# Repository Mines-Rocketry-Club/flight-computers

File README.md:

# Mines Rocket Club Flight Computer Development
## Scope
The series of flight computers produced as part of this project are inteneded to be useable for any low or high power rocketry applications.
These will also span a large range of cost in order to provide flight computer capabilities for very high risk and experimental flights.
The lowest possible trim level is a CW RF emmiter intended for use with radio direction finding equipment.
The highest trim level will provide a platform for executing user space code asynchronously from the main event loop of the flight computer.
## Standards
- No features* will be lost when moving up in trim levels.
<br>
*The Screamer's CW Emmiter is lost as the other telemetry hardware on the board can be used to locate the device.

## Trim Levels
|Name         |Features                                                                         |Weight |Cost (2024) |
|-------------|---------------------------------------------------------------------------------|-------|------------|
|The Screamer | CW RF Emitter                                                                   | 5g    | 5$         |
|The Timer    | 3 Axis Accelerometer, Barometric Altimiter, CP1200 Transmitter, 4 Pyro Channels | 10g   | 20$        |
|The Guesser  | GPS, Onboard Data Logging, WIFI based configuration                             | 15g   | 40$        |
|The Knower   | User Code Execution, High Frequency Data Logging, 8 Pyro Channels               | 20g   | 60$        |

## System Architectures
### The Screamer
#### Usage
This board emits a constant signal at 146.660 MHz.
This signal can be recived by many common low-cost trancievers, such as the Baofeng UV-5RA, UV8W, and AR-5RM.
With a directional antenna any of these trancievers provides radio direction finding capabilities to the system.
#### Design
The sysem does not have a microcontroller or any other regualtion system.
It consistis of a power supply, based on the <PART NAME> and the transmitter, which is a MAX2606 IF Oscillator.
This component is not intended to be used to drive an antenna directly, however, the internal 50Ω matching and the -10dBm power output provide enough for this usage.
In order to capture the full -10dBm output, a loop antenna must be attached to ***BOTH*** of the provided antenna pads.
Bare copper wire or thin coat magnet wire is recommened for the antenna. a single loop in the wire should be adequate for most applicatons.

Due to the extremley low power consumption of the system, it can be powered parasitically off of any of the other computers in this series.
> Attachement points will be added in the next revisions of each of the boards
> - [ ] The Timer
> - [ ] The Guesser
> - [ ] The Knower

### The Timer
#### Usage
#### Design
### The Guesser
### The Knower
## License
All hardware contained within this repository is under the TAPR Open Hardware License (OHL), which can be found, in full, in `HW_LICENSE`.
All software contained within this repository is under the GPL, which can be found, in full, in `FW_LICENSE`.

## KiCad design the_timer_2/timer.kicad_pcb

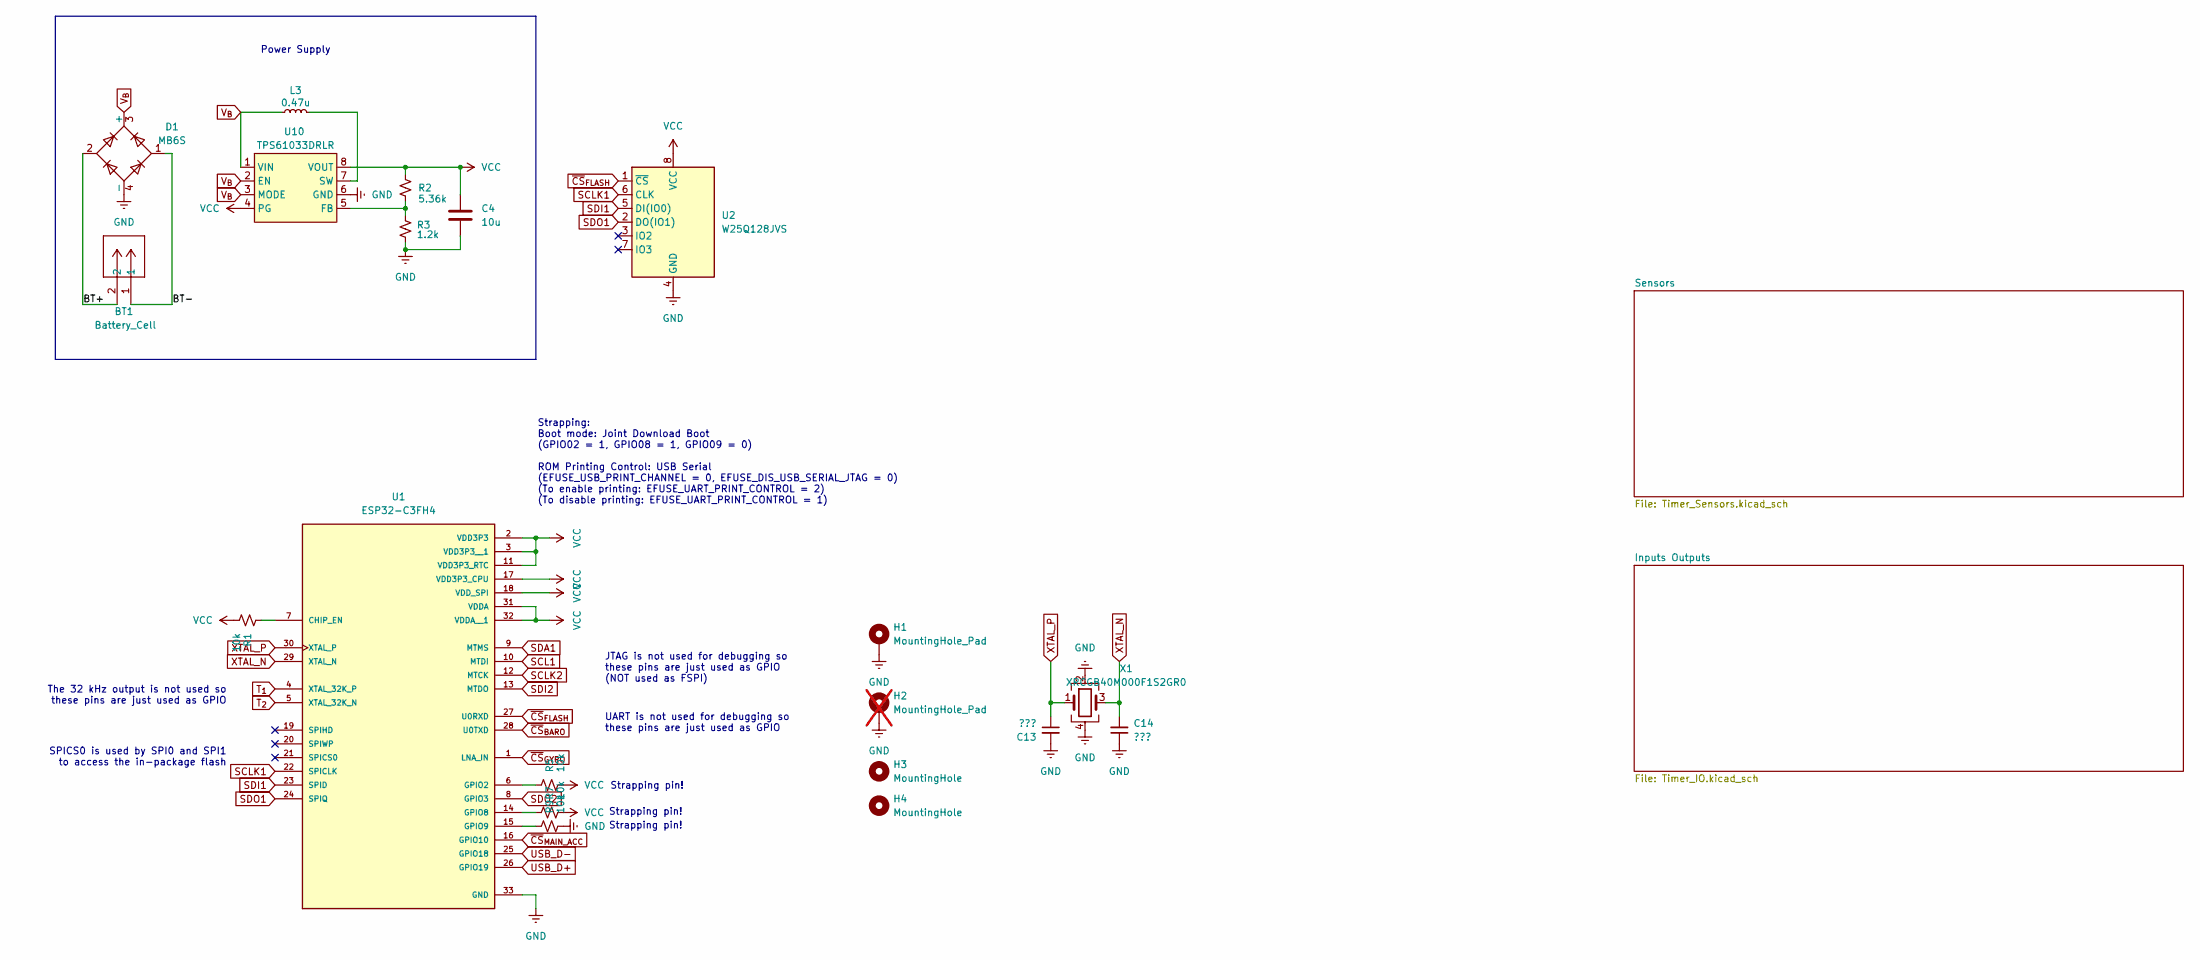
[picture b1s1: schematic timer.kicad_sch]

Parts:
BT1: Battery_Cell; CONN2_1775469-2_TEC
C4: 10u; C_0603_1608Metric
C13, C14: ???; C_0603_1608Metric
D1: MB6S; TO-269AA
H1: MountingHole_Pad; MountingHole_3.2mm_M3_Pad
H2: MountingHole_Pad; MountingHole_3.2mm_M3_Pad; not fitted
H3, H4: MountingHole; MountingHole_3.2mm_M3
L3: 0.47u; L_0603_1608Metric
R1, R5, R7, R9: 10k; R_0603_1608Metric
R2: 5.36k; R_0603_1608Metric
R3: 1.2k; R_0603_1608Metric
U1: ESP32-C3FH4; QFN-32-1EP_5x5mm_P0.5mm_EP3.7x3.7mm; PARTREV V1.0
U2: W25Q128JVS; SOIC-8_5.23x5.23mm_P1.27mm
U10: TPS61033DRLR; SOT-583-8
X1: XRCGB40M000F1S2GR0; Crystal_SMD_2016-4Pin_2.0x1.6mm

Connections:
/BT+: BT1.2, D1.2
/BT-: BT1.1, D1.1
GND: C4.2, C13.2, C14.1, D1.4 (-), H1.1, H2.1, R3.2, R9.2, U1.33 (GND), U2.4 (GND), U10.6 (GND), X1.2, X1.4; also elsewhere on the board
unnamed: R1.1, U1.7 (CHIP_EN)
unnamed: R5.1, U1.6 (GPIO2)
unnamed: R7.1, U1.14 (GPIO8)
unnamed: R9.1, U1.15 (GPIO9)
unnamed: R2.2, R3.1, U10.5 (FB)
unnamed: L3.1, U10.7 (SW)
SCL1: U1.10 (MTDI)
SCLK1: U1.22 (SPICLK), U2.6 (CLK)
SCLK2: U1.12 (MTCK); also elsewhere on the board
SDA1: U1.9 (MTMS)
SDI1: U1.23 (SPID), U2.5 (DI(IO0))
SDI2: U1.13 (MTDO); also elsewhere on the board
SDO1: U1.24 (SPIQ), U2.2 (DO(IO1))
SDO2: U1.8 (GPIO3); also elsewhere on the board
T_{1}: U1.4 (XTAL_32K_P); also elsewhere on the board
T_{2}: U1.5 (XTAL_32K_N); also elsewhere on the board
USB_D+: U1.26 (GPIO19); also elsewhere on the board
USB_D-: U1.25 (GPIO18); also elsewhere on the board
VCC: C4.1, R1.2, R2.1, R5.2, R7.2, U1.2 (VDD3P3), U1.3 (VDD3P3__1), U1.11 (VDD3P3_RTC), U1.17 (VDD3P3_CPU), U1.18 (VDD_SPI), U1.31 (VDDA), U1.32 (VDDA__1), U2.8 (VCC), U10.4 (PG), U10.8 (VOUT); also elsewhere on the board
V_{B}: D1.3 (+), L3.2, U10.1 (VIN), U10.2 (EN), U10.3 (MODE); also elsewhere on the board
XTAL_N: C14.2, U1.29 (XTAL_N), X1.3
XTAL_P: C13.1, U1.30 (XTAL_P), X1.1
~CS_{BARO}: U1.28 (U0TXD); also elsewhere on the board
~CS_{FLASH}: U1.27 (U0RXD), U2.1 (~CS)
~CS_{GYRO}: U1.1 (LNA_IN); also elsewhere on the board
~CS_{MAIN_ACC}: U1.16 (GPIO10); also elsewhere on the board

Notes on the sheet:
Strapping: Boot mode: Joint Download Boot (GPIO02 = 1, GPIO08 = 1, GPIO09 = 0) ROM Printing Control: USB Serial (EFUSE_USB_PRINT_CHANNEL = 0, EFUSE_DIS_USB_SERIAL_JTAG = 0) (To enable printing: EFUSE_UART_PRINT_CONTROL = 2) (To disable printing: EFUSE_UART_PRINT_CONTROL = 1)
UART is not used for debugging so these pins are just used as GPIO
SPICS0 is used by SPI0 and SPI1 to access the in-package flash
Strapping pin!
JTAG is not used for debugging so these pins are just used as GPIO (NOT used as FSPI)
Power Supply
The 32 kHz output is not used so these pins are just used as GPIO

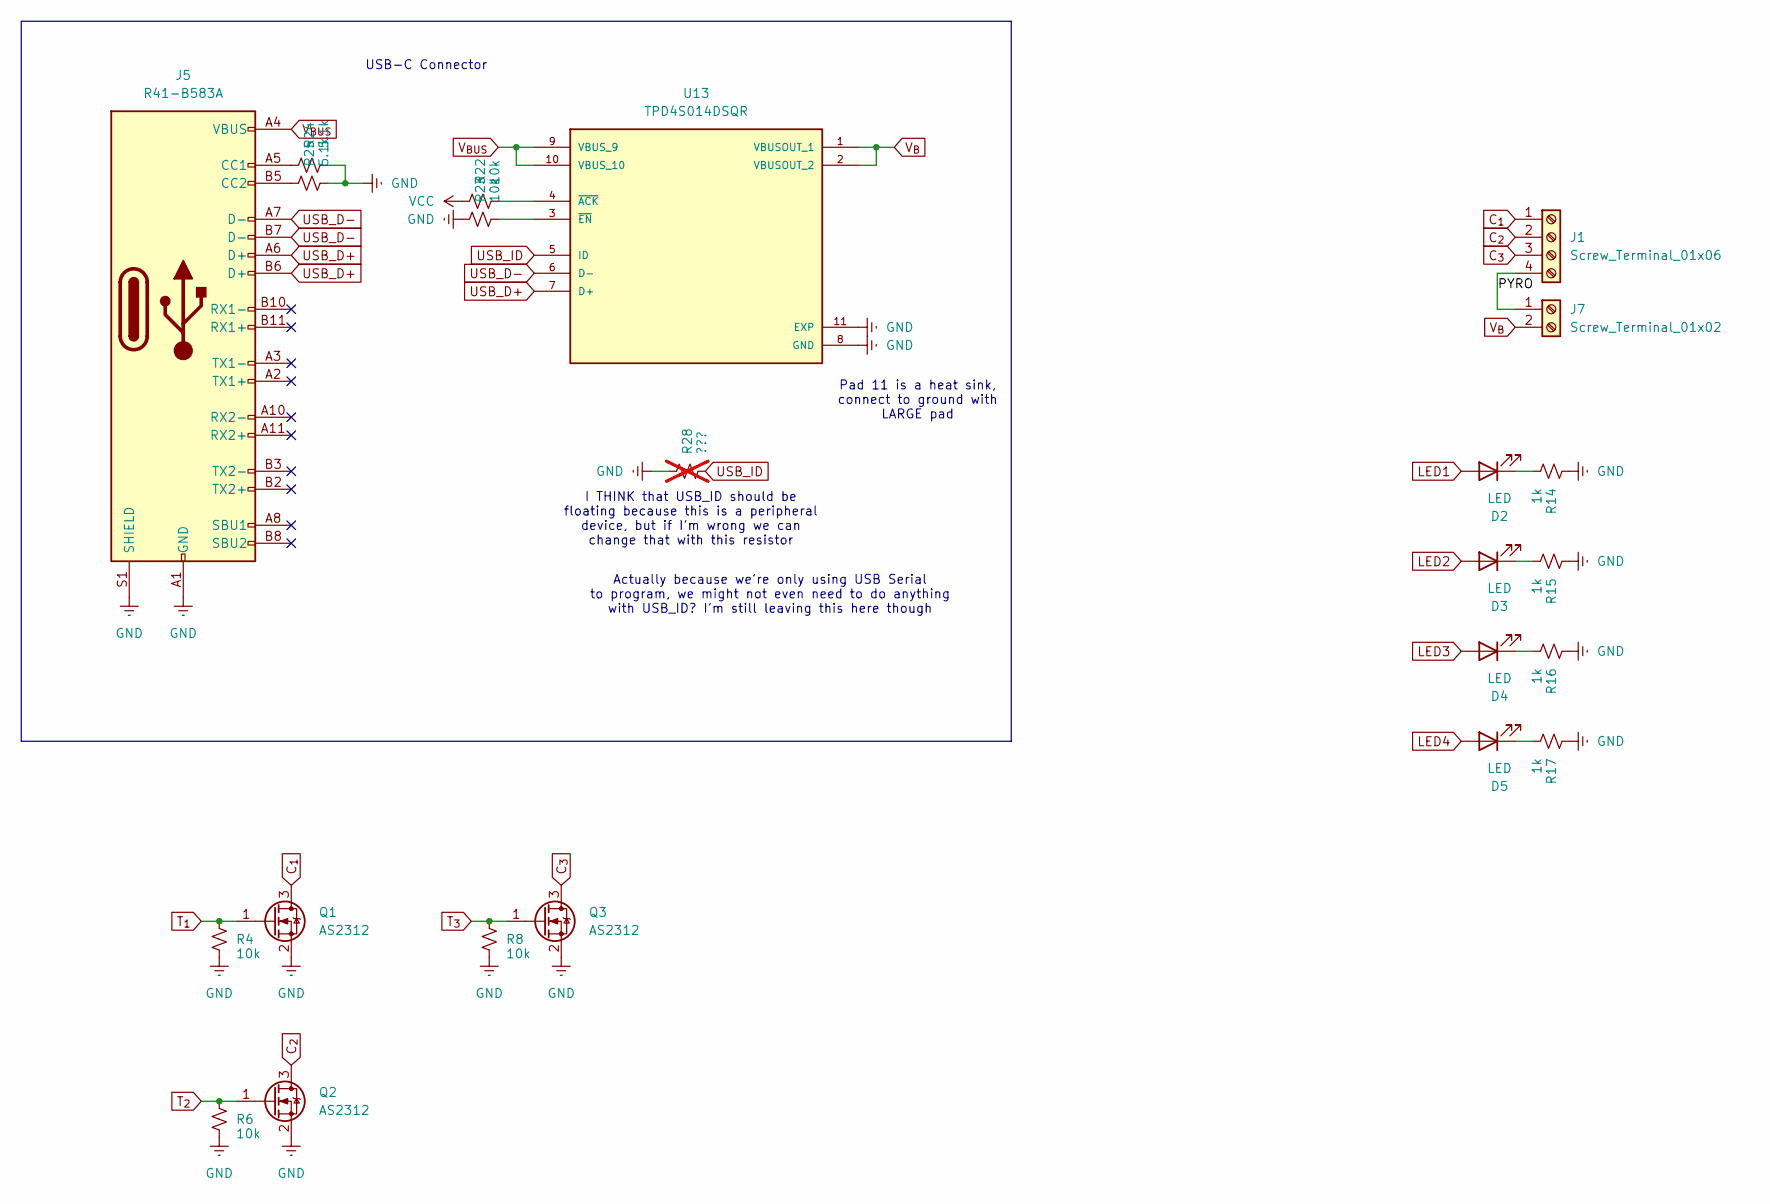
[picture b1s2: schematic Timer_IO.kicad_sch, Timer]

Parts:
D2, D3, D4, D5: LED; LED_0603_1608Metric
J1: Screw_Terminal_01x06; TerminalBlock_Phoenix_MPT-0,5-4-2.54_1x04_P2.54mm_Horizontal
J5: R41-B583A; CONN_R41-B583A_MIT
J7: Screw_Terminal_01x02; TerminalBlock_Phoenix_MPT-0,5-2-2.54_1x02_P2.54mm_Horizontal
Q1, Q2, Q3: AS2312; SOT-23
R4, R6, R8, R22, R23: 10k; R_0603_1608Metric
R14, R15, R16, R17: 1k; R_0603_1608Metric
R24, R25: 5.1k; R_0603_1608Metric
R28: ???; R_0603_1608Metric; not fitted
U13: TPD4S014DSQR; PARTREV E

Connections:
/Inputs Outputs/PYRO: J1.4, J7.1
C_{1}: J1.1, Q1.3 (D)
C_{2}: J1.2, Q2.3 (D)
C_{3}: J1.3, Q3.3 (D)
GND: J5.A1 (GND), J5.A12 (GND), J5.B1 (GND), J5.B12 (GND), J5.S1 (SHIELD), Q1.2 (S), Q2.2 (S), Q3.2 (S), R4.2, R6.2, R8.2, R14.1, R15.1, R16.1, R17.1, R23.1, R24.2, R25.2, R28.1, U13.8 (GND), U13.11 (EXP); also elsewhere on the board
LED1: D2.2 (A)
LED2: D3.2 (A)
LED3: D4.2 (A)
LED4: D5.2 (A)
unnamed: D2.1 (K), R14.2
unnamed: D3.1 (K), R15.2
unnamed: D4.1 (K), R16.2
unnamed: D5.1 (K), R17.2
unnamed: J5.A5 (CC1), R24.1
unnamed: J5.B5 (CC2), R25.1
unnamed: R22.2, U13.4 (~ACK)
unnamed: R23.2, U13.3 (~EN)
T_{1}: Q1.1 (G), R4.1; also elsewhere on the board
T_{2}: Q2.1 (G), R6.1; also elsewhere on the board
T_{3}: Q3.1 (G), R8.1
USB_D+: J5.A6 (D+), J5.B6 (D+), U13.7 (D+); also elsewhere on the board
USB_D-: J5.A7 (D-), J5.B7 (D-), U13.6 (D-); also elsewhere on the board
USB_ID: R28.2, U13.5 (ID)
VCC: R22.1; also elsewhere on the board
V_{BUS}: J5.A4 (VBUS), J5.A9 (VBUS), J5.B4 (VBUS), J5.B9 (VBUS), U13.9 (VBUS_9), U13.10 (VBUS_10)
V_{B}: J7.2, U13.1 (VBUSOUT_1), U13.2 (VBUSOUT_2); also elsewhere on the board

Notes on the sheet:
I THINK that USB_ID should be floating because this is a peripheral device, but if I'm wrong we can change that with this resistor
USB-C Connector
Actually because we're only using USB Serial to program, we might not even need to do anything with USB_ID? I'm still leaving this here though
Pad 11 is a heat sink, connect to ground with LARGE pad

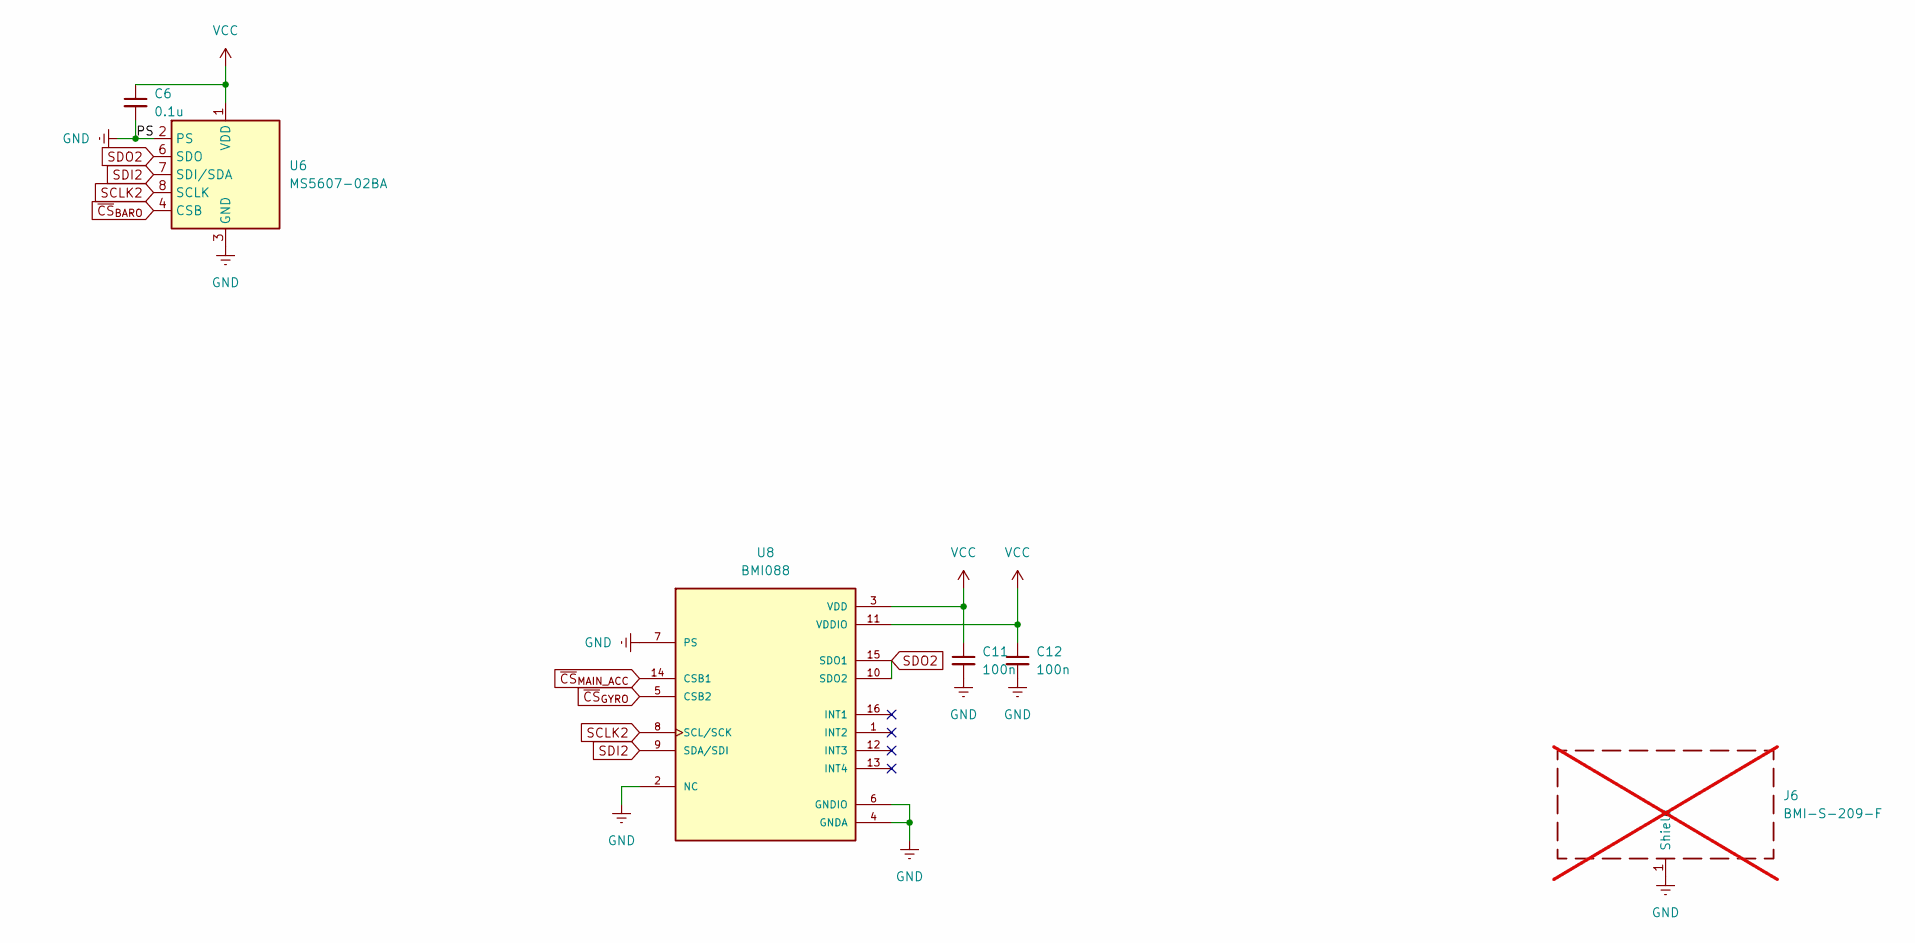
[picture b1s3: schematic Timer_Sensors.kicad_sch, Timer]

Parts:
C6: 0.1u; C_0603_1608Metric
C11, C12: 100n; C_0603_1608Metric
J6: BMI-S-209-F; Laird_Technologies_BMI-S-209-F_29.36x18.50mm; not fitted
U6: MS5607-02BA; LGA-8_3x5mm_P1.25mm
U8: BMI088

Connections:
GND: C6.2, C11.2, C12.2, J6.1, U6.2 (PS), U6.3 (GND), U8.2 (NC), U8.4 (GNDA), U8.6 (GNDIO), U8.7 (PS); also elsewhere on the board
SCLK2: U6.8 (SCLK), U8.8 (SCL/SCK); also elsewhere on the board
SDI2: U6.7 (SDI/SDA), U8.9 (SDA/SDI); also elsewhere on the board
SDO2: U6.6 (SDO), U8.10 (SDO2), U8.15 (SDO1); also elsewhere on the board
VCC: C6.1, C11.1, C12.1, U6.1 (VDD), U8.3 (VDD), U8.11 (VDDIO); also elsewhere on the board
~CS_{BARO}: U6.4 (CSB), U6.5 (CSB); also elsewhere on the board
~CS_{GYRO}: U8.5 (CSB2); also elsewhere on the board
~CS_{MAIN_ACC}: U8.14 (CSB1); also elsewhere on the board

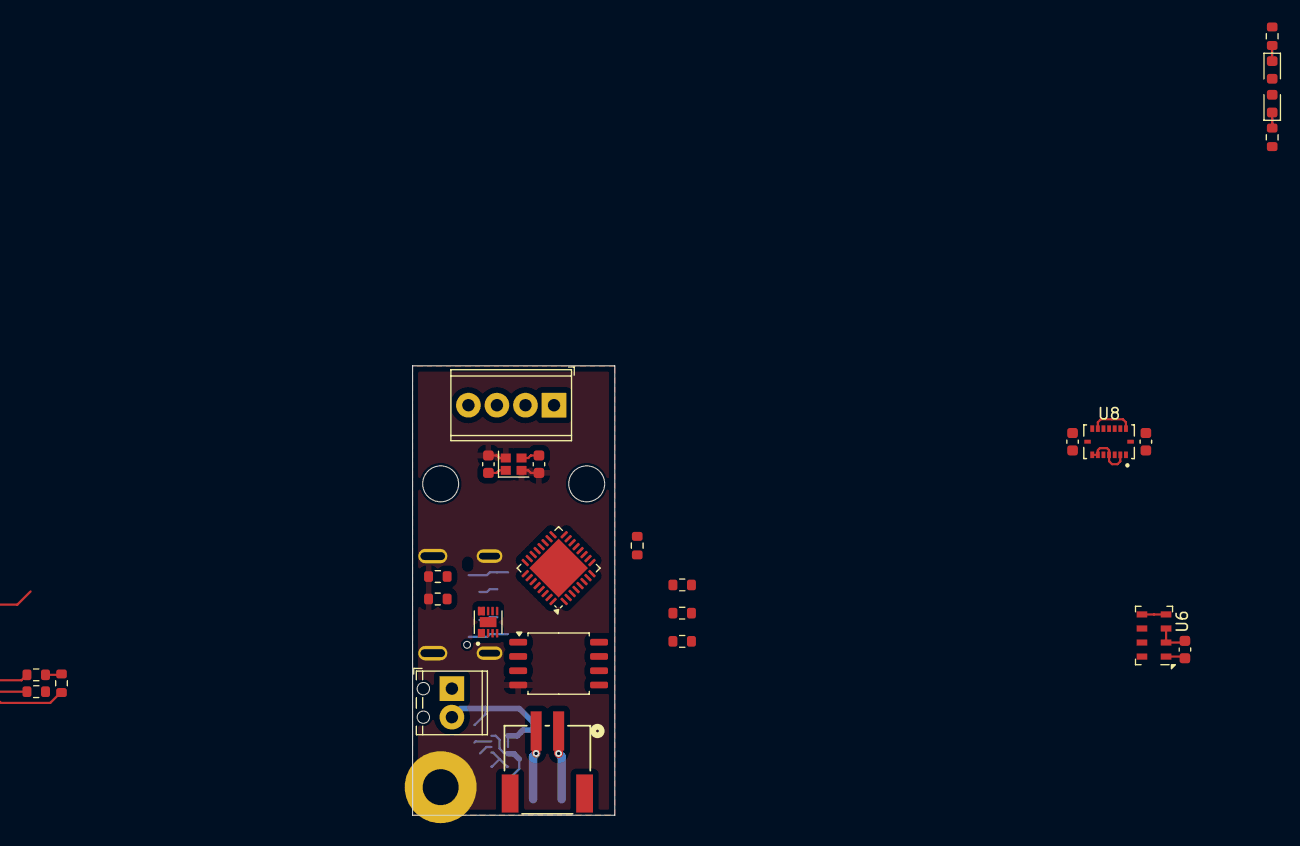
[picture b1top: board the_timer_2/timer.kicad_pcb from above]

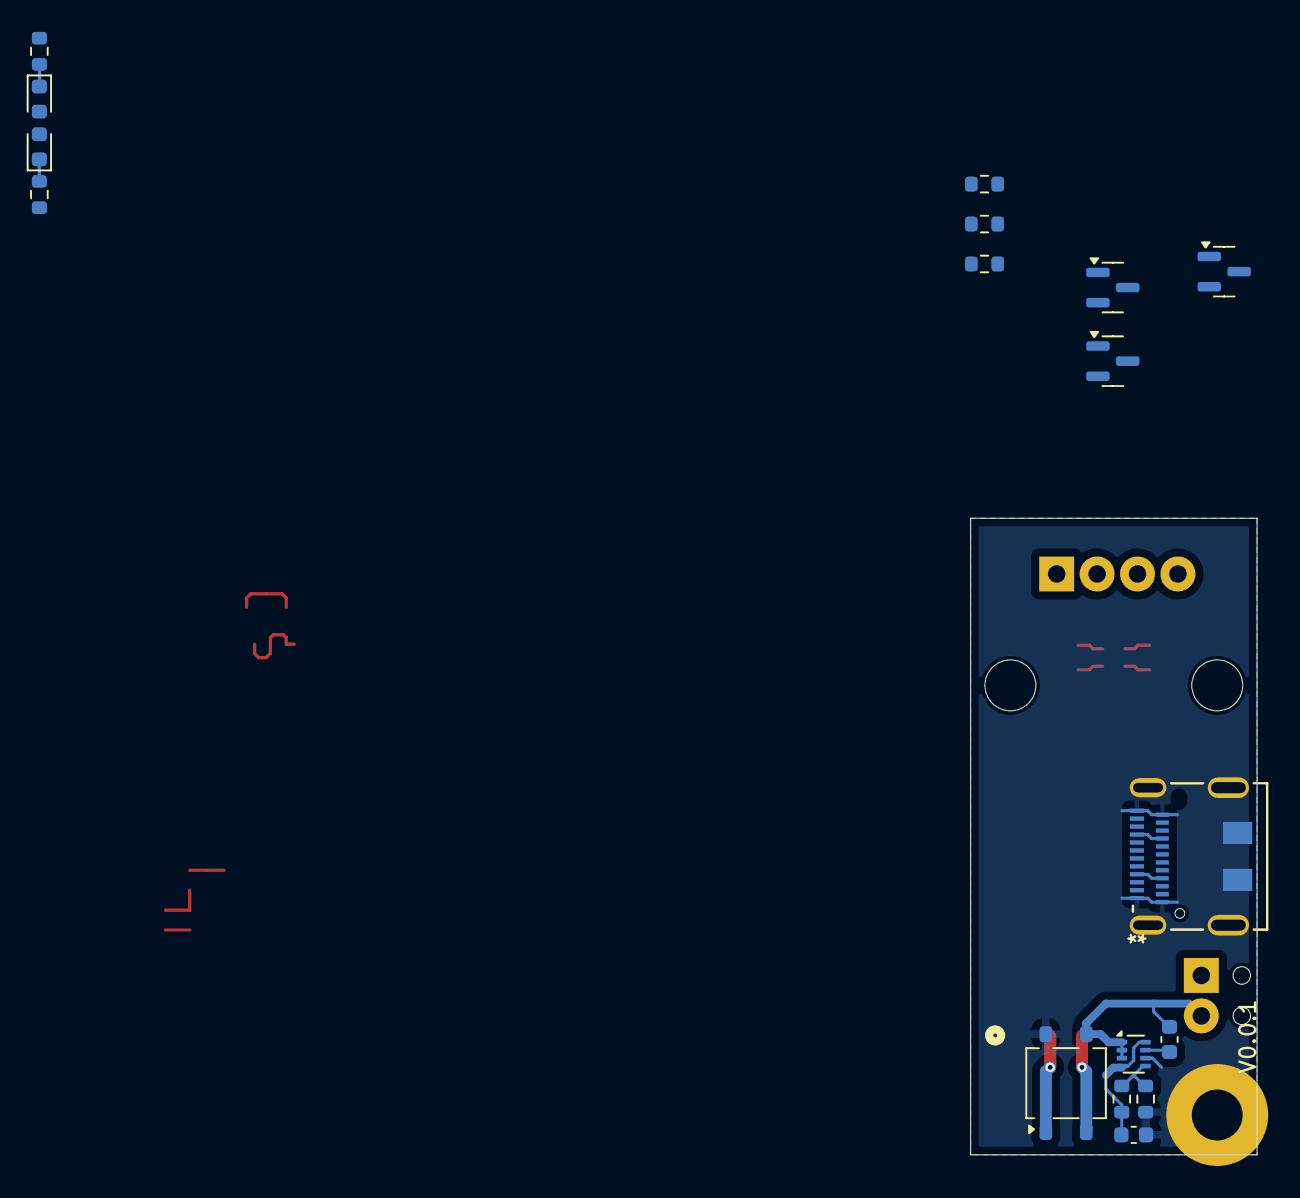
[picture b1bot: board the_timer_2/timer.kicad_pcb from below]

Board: 2 copper layers, 18.0 x 40.0 mm, 47 parts (17 on the bottom side), 42 nets.

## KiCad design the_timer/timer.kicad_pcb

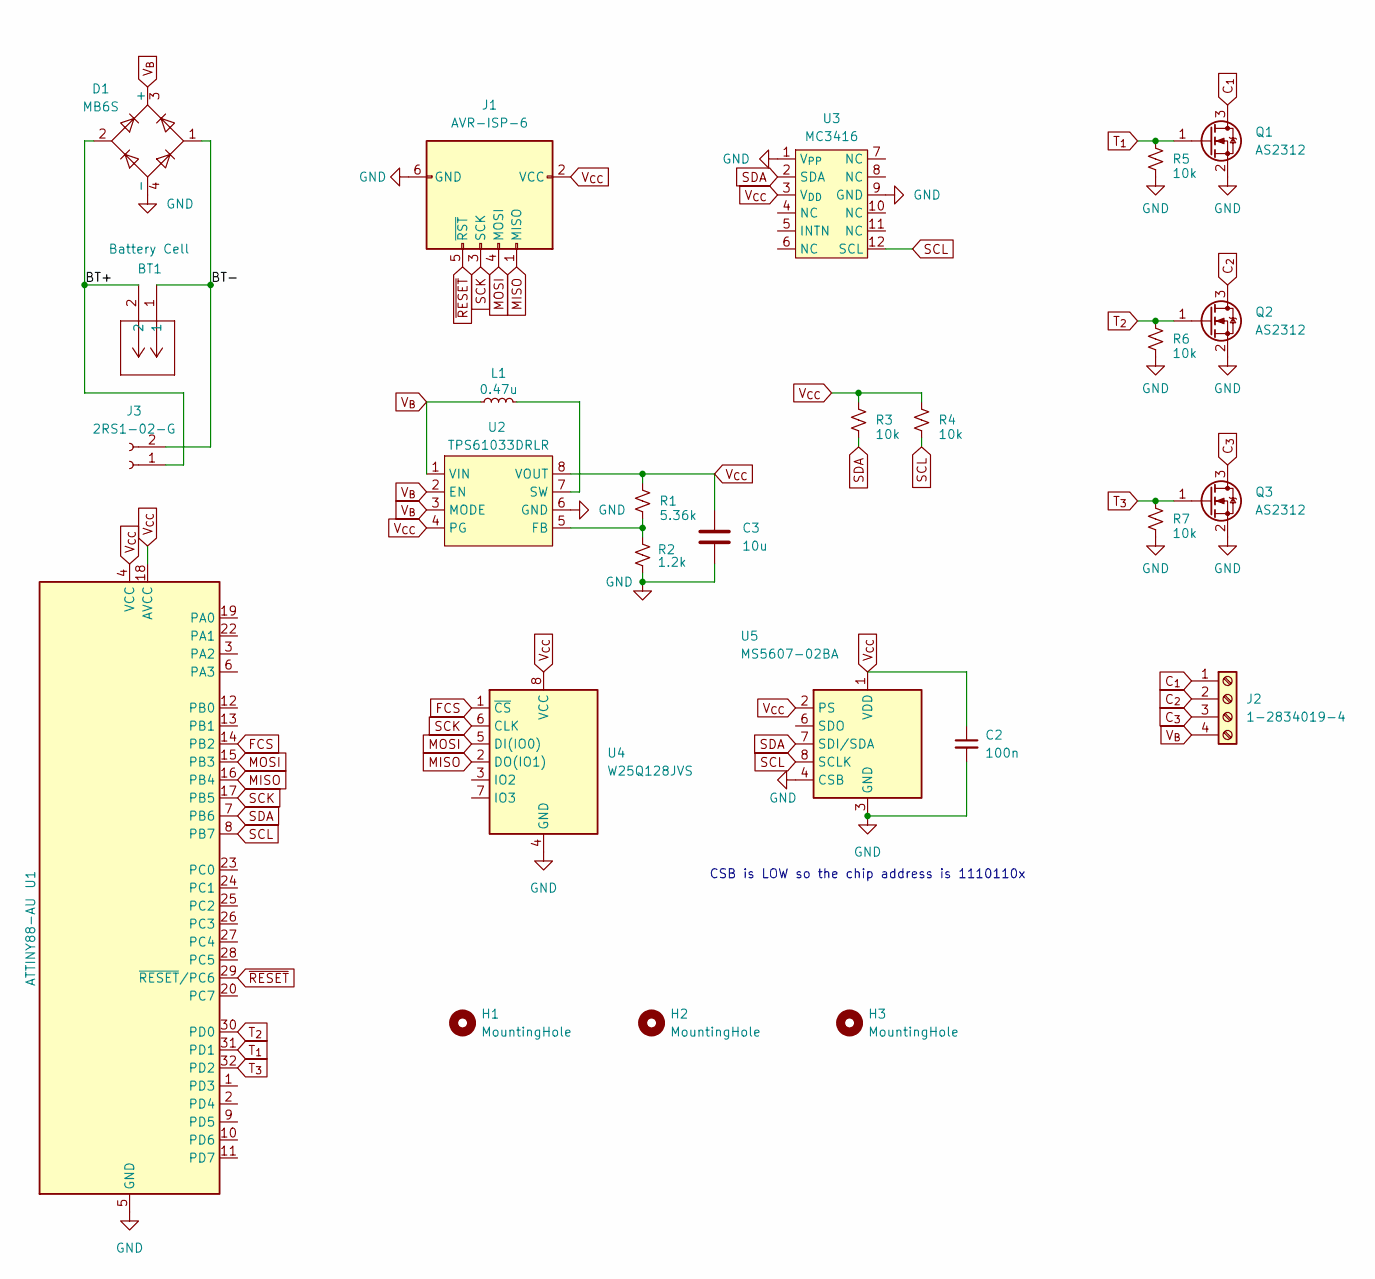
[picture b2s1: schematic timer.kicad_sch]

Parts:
BT1: Battery Cell; CONN2_1775469-2_TEC
C2: 100n; C_0603_1608Metric
C3: 10u; C_0603_1608Metric
D1: MB6S; TO-269AA
H1, H2, H3: MountingHole; MountingHole_3.2mm_M3
J1: AVR-ISP-6; PinHeader_2x03_P1.27mm_Vertical
J2: 1-2834019-4; TE_1-2834019-4
J3: 2RS1-02-G; PinSocket_1x02_P2.00mm_Vertical
L1: 0.47u; L_0603_1608Metric
Q1, Q2, Q3: AS2312; SOT-23
R1: 5.36k; R_0603_1608Metric
R2: 1.2k; R_0603_1608Metric
R3, R4, R5, R6, R7: 10k; R_0603_1608Metric
U1: ATTINY88-AU; TQFP-32_7x7mm_P0.8mm
U2: TPS61033DRLR; SOT-583-8
U3: MC3416; Kionix_LGA-12_2x2mm_P0.5mm_LayoutBorder2x4y
U4: W25Q128JVS; SOIC-8_5.23x5.23mm_P1.27mm
U5: MS5607-02BA; LGA-8_3x5mm_P1.25mm

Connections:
/BT+: BT1.2, D1.2, J3.1
/BT-: BT1.1, D1.1, J3.2
C_{1}: J2.1, Q1.3 (D)
C_{2}: J2.2, Q2.3 (D)
C_{3}: J2.3, Q3.3 (D)
FCS: U1.14 (PB2), U4.1 (~CS)
GND: C2.2, C3.2, D1.4 (-), J1.6 (GND), Q1.2 (S), Q2.2 (S), Q3.2 (S), R2.2, R5.2, R6.2, R7.2, U1.5 (GND), U1.21 (GND), U2.6 (GND), U3.1 (V_{PP}), U3.9 (GND), U4.4 (GND), U5.3 (GND), U5.4 (CSB), U5.5 (CSB)
MISO: J1.1 (MISO), U1.16 (PB4), U4.2 (DO(IO1))
MOSI: J1.4 (MOSI), U1.15 (PB3), U4.5 (DI(IO0))
unnamed: R1.2, R2.1, U2.5 (FB)
unnamed: L1.1, U2.7 (SW)
SCK: J1.3 (SCK), U1.17 (PB5), U4.6 (CLK)
SCL: R4.2, U1.8 (PB7), U3.12 (SCL), U5.8 (SCLK)
SDA: R3.2, U1.7 (PB6), U3.2 (SDA), U5.7 (SDI/SDA)
T_{1}: Q1.1 (G), R5.1, U1.31 (PD1)
T_{2}: Q2.1 (G), R6.1, U1.30 (PD0)
T_{3}: Q3.1 (G), R7.1, U1.32 (PD2)
V_{B}: D1.3 (+), J2.4, L1.2, U2.1 (VIN), U2.2 (EN), U2.3 (MODE)
V_{CC}: C2.1, C3.1, J1.2 (VCC), R1.1, R3.1, R4.1, U1.4 (VCC), U1.18 (AVCC), U2.4 (PG), U2.8 (VOUT), U3.3 (V_{DD}), U4.8 (VCC), U5.1 (VDD), U5.2 (PS)
~RESET: J1.5 (~RST), U1.29 (~RESET/PC6)

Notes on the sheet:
CSB is LOW so the chip address is 1110110x

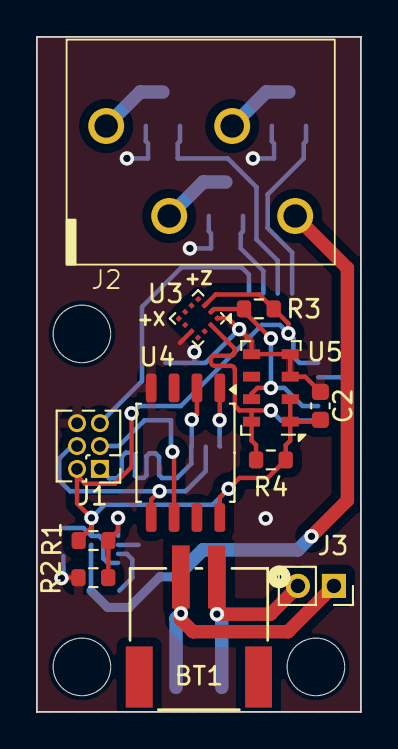
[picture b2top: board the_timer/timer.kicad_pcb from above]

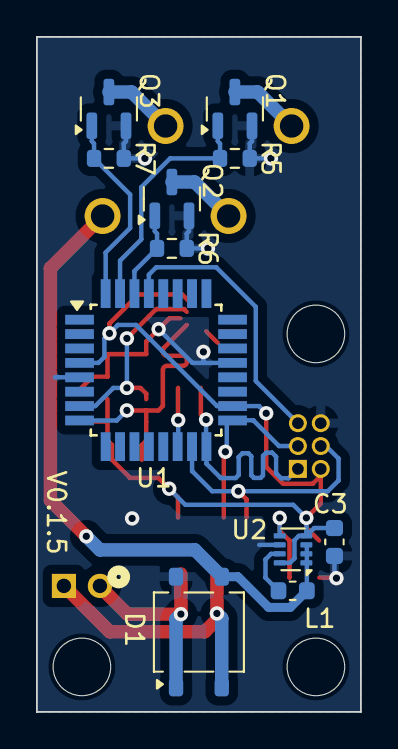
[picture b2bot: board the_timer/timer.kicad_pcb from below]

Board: 2 copper layers, 18.0 x 37.5 mm, 26 parts (11 on the bottom side), 20 nets.

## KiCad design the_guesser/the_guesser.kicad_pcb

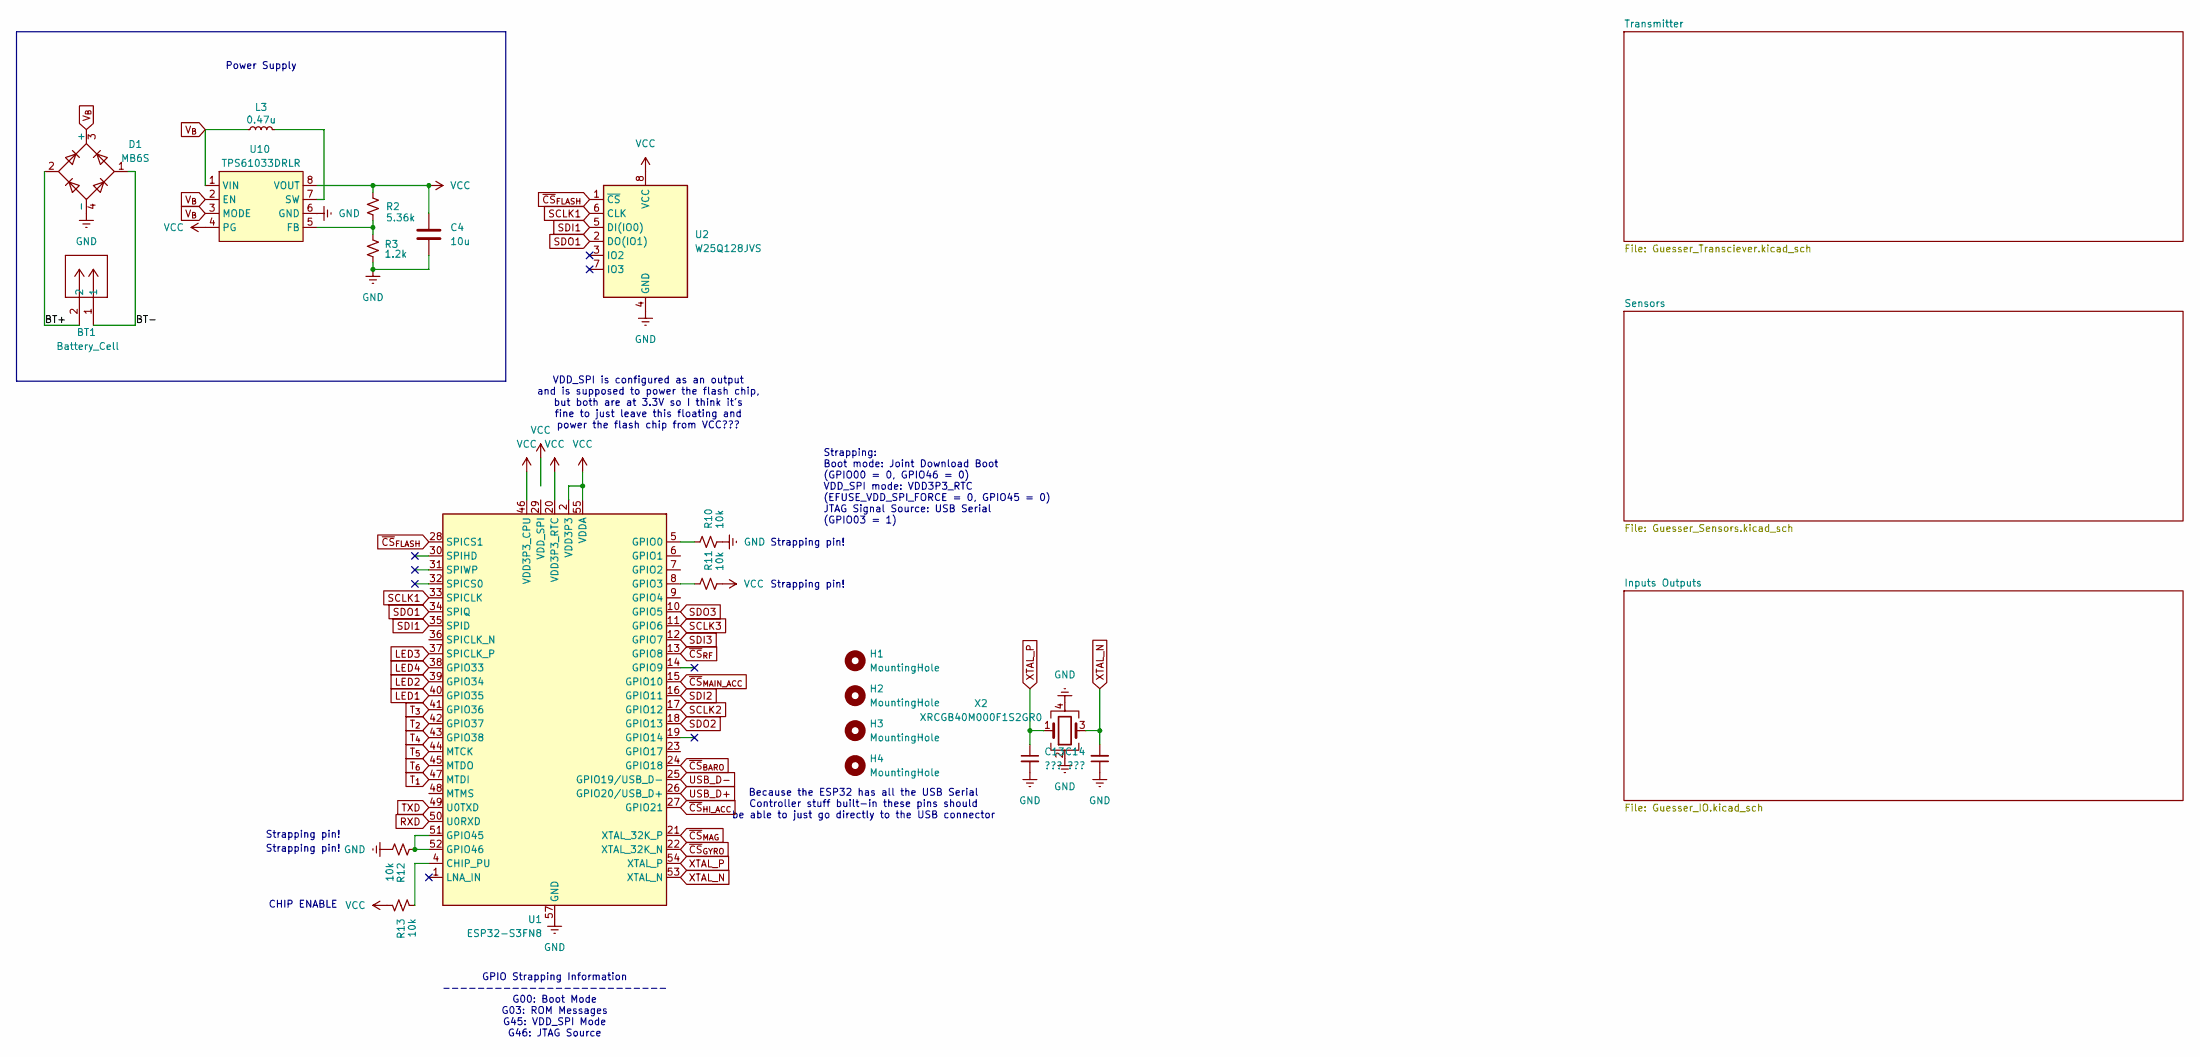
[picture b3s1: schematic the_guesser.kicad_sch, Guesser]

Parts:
BT1: Battery_Cell; CONN2_1775469-2_TEC
C4: 10u; C_0603_1608Metric
C13, C14: ???; C_0603_1608Metric
D1: MB6S; TO-269AA
H1, H2, H3, H4: MountingHole; MountingHole_3.2mm_M3
L3: 0.47u; L_0603_1608Metric
R2: 5.36k; R_0603_1608Metric
R3: 1.2k; R_0603_1608Metric
R10, R11, R12, R13: 10k; R_0603_1608Metric
U1: ESP32-S3FN8; QFN-56-1EP_7x7mm_P0.4mm_EP4x4mm
U2: W25Q128JVS; SOIC-8_5.23x5.23mm_P1.27mm
U10: TPS61033DRLR; SOT-583-8
X2: XRCGB40M000F1S2GR0; Crystal_SMD_2016-4Pin_2.0x1.6mm

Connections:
/BT+: BT1.2, D1.2
/BT-: BT1.1, D1.1
GND: C4.2, C13.2, C14.1, D1.4 (-), R3.2, R10.2, R12.2, U1.57 (GND), U2.4 (GND), U10.6 (GND), X2.2, X2.4; also elsewhere on the board
LED1: U1.40 (GPIO35); also elsewhere on the board
LED2: U1.39 (GPIO34); also elsewhere on the board
LED3: U1.37 (SPICLK_P); also elsewhere on the board
LED4: U1.38 (GPIO33); also elsewhere on the board
unnamed: R13.2, U1.4 (CHIP_PU)
unnamed: R10.1, U1.5 (GPIO0)
unnamed: R11.1, U1.8 (GPIO3)
unnamed: R12.1, U1.51 (GPIO45), U1.52 (GPIO46)
unnamed: R2.2, R3.1, U10.5 (FB)
unnamed: L3.1, U10.7 (SW)
RXD: U1.50 (U0RXD); also elsewhere on the board
SCLK1: U1.33 (SPICLK), U2.6 (CLK)
SCLK2: U1.17 (GPIO12); also elsewhere on the board
SCLK3: U1.11 (GPIO6); also elsewhere on the board
SDI1: U1.35 (SPID), U2.5 (DI(IO0))
SDI2: U1.16 (GPIO11); also elsewhere on the board
SDI3: U1.12 (GPIO7); also elsewhere on the board
SDO1: U1.34 (SPIQ), U2.2 (DO(IO1))
SDO2: U1.18 (GPIO13); also elsewhere on the board
SDO3: U1.10 (GPIO5); also elsewhere on the board
TXD: U1.49 (U0TXD); also elsewhere on the board
T_{1}: U1.47 (MTDI); also elsewhere on the board
T_{2}: U1.42 (GPIO37); also elsewhere on the board
T_{3}: U1.41 (GPIO36); also elsewhere on the board
T_{4}: U1.43 (GPIO38); also elsewhere on the board
T_{5}: U1.44 (MTCK); also elsewhere on the board
T_{6}: U1.45 (MTDO); also elsewhere on the board
USB_D+: U1.26 (GPIO20/USB_D+); also elsewhere on the board
USB_D-: U1.25 (GPIO19/USB_D-); also elsewhere on the board
VCC: C4.1, R2.1, R11.2, R13.1, U1.2 (VDD3P3), U1.3 (VDD3P3), U1.20 (VDD3P3_RTC), U1.46 (VDD3P3_CPU), U1.55 (VDDA), U1.56 (VDDA), U2.8 (VCC), U10.4 (PG), U10.8 (VOUT); also elsewhere on the board
V_{B}: D1.3 (+), L3.2, U10.1 (VIN), U10.2 (EN), U10.3 (MODE); also elsewhere on the board
XTAL_N: C14.2, U1.53 (XTAL_N), X2.3
XTAL_P: C13.1, U1.54 (XTAL_P), X2.1
~CS_{BARO}: U1.24 (GPIO18); also elsewhere on the board
~CS_{FLASH}: U1.28 (SPICS1), U2.1 (~CS)
~CS_{GYRO}: U1.22 (XTAL_32K_N); also elsewhere on the board
~CS_{HI_ACC}: U1.27 (GPIO21); also elsewhere on the board
~CS_{MAG}: U1.21 (XTAL_32K_P); also elsewhere on the board
~CS_{MAIN_ACC}: U1.15 (GPIO10); also elsewhere on the board
~CS_{RF}: U1.13 (GPIO8); also elsewhere on the board

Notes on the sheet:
VDD_SPI is configured as an output and is supposed to power the flash chip, but both are at 3.3V so I think it's fine to just leave this floating and power the flash chip from VCC???
Strapping pin!
Strapping: Boot mode: Joint Download Boot (GPIO00 = 0, GPIO46 = 0) VDD_SPI mode: VDD3P3_RTC (EFUSE_VDD_SPI_FORCE = 0, GPIO45 = 0) JTAG Signal Source: USB Serial (GPIO03 = 1)
GPIO Strapping Information -------------------------- G00: Boot Mode G03: ROM Messages G45: VDD_SPI Mode G46: JTAG Source
Power Supply
Because the ESP32 has all the USB Serial Controller stuff built-in these pins should be able to just go directly to the USB connector
CHIP ENABLE
